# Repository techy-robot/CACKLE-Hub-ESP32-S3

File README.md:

---
modified: 2025-11-07T22:07:35-07:00
---

# ESP32-S3 Hub

> [!TIP]
> This board is part of a larger modular control board ecosystem, [CACKLE](https://github.com/techy-robot/CACKLE)

This is a 4-driver hub based on the Espressif ESP32-S3FH4 chip. It has two cores powerful running at 240 mhz, and 4mb of flash memory. Other variants of the ESP32-S3 can be used as long as they have built in flash memory.

The ESP32-S3 chip does not *quite* have enough pins for driving 4 motors and several sensors, so some cuts were made. For example, on all 4 ports for the ADCs, only two out of three pins are actually connected. This will work for brushed and brushless FOC control, but it may not work for other use cases. I also had to use the USB lines for a tri-state shift register, which controls all the SPI chip select lines. I am planning on programming the chip via UART, which means that the RS485 lines must be disconnected.

The SPI bus should be able to operate at 80mhz, though this has not been tested yet. For all practical use-cases I am limiting this to 20mhz.

Partial 3D picture (headers not shown)

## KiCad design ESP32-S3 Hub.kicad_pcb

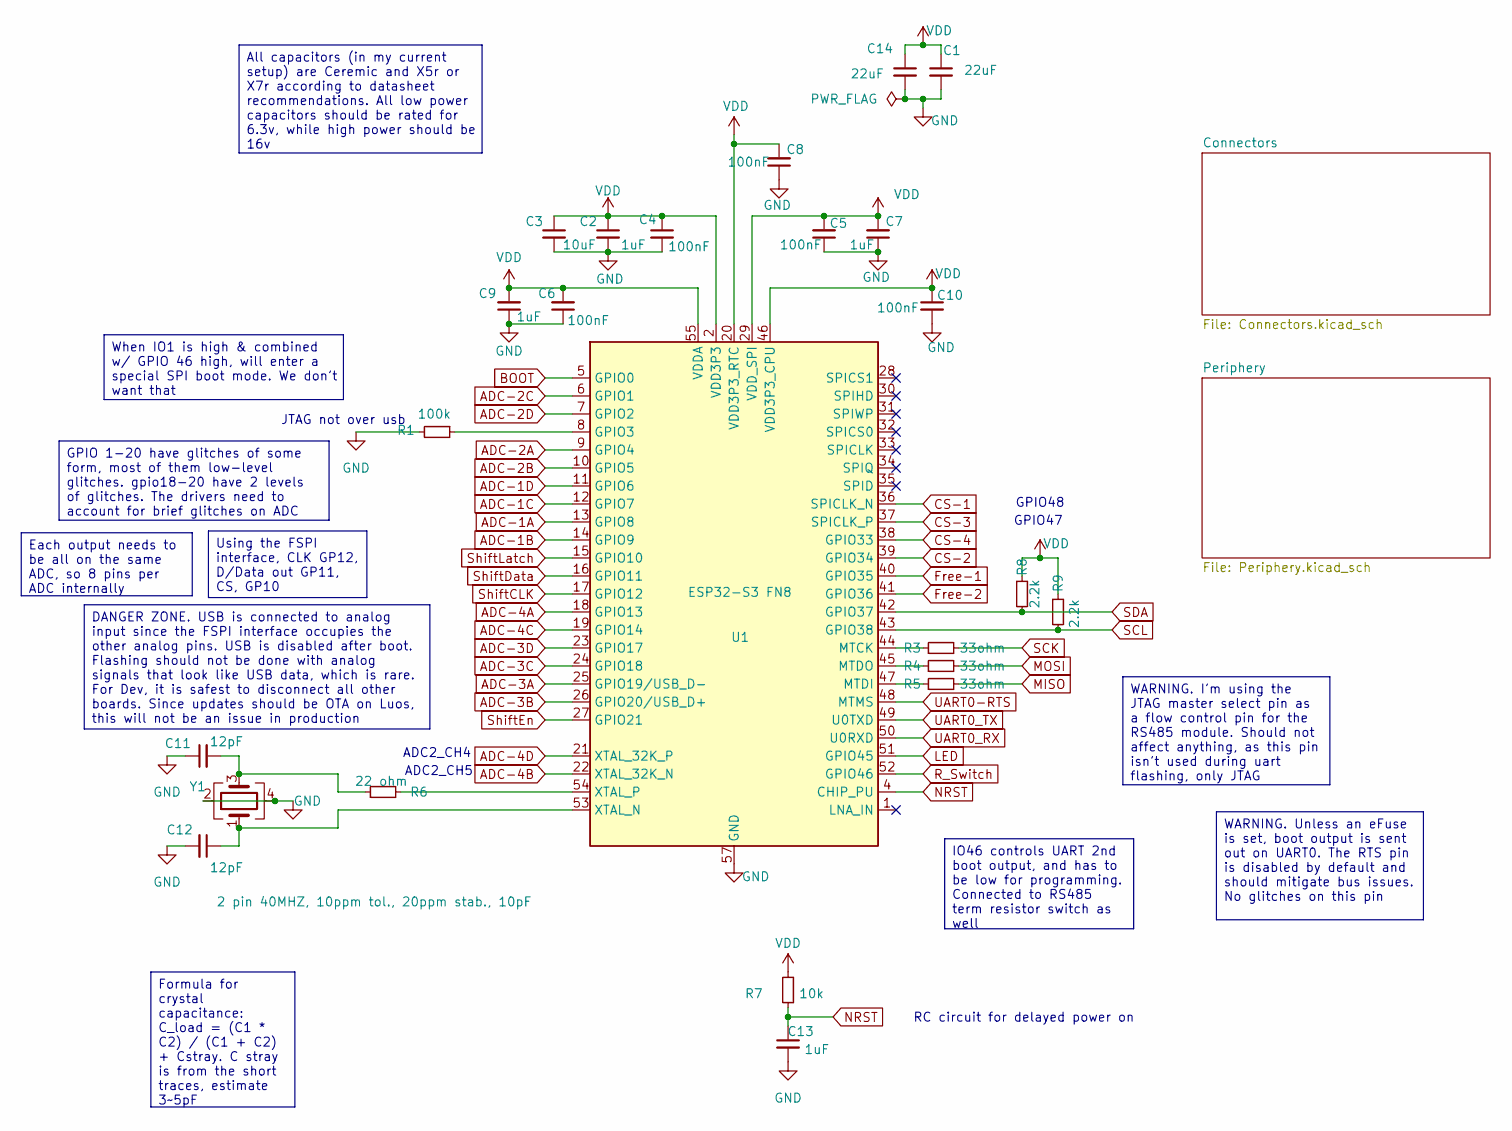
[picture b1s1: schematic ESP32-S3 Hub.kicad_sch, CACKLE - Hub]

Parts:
C1, C14: 22uF; C_0402_1005Metric; LCSC C415703
C2, C7, C9, C13: 1uF; C_0402_1005Metric; LCSC C52923
C3: 10uF; C_0402_1005Metric; LCSC C15525
C4, C5, C6, C8, C10: 100nF; C_0402_1005Metric; LCSC C1525
C11, C12: 12pF; C_0201_0603Metric; LCSC C384960
R1: 100k; R_0402_1005Metric; LCSC C25741
R3, R4, R5: 33ohm; R_0402_1005Metric; LCSC C25105
R6: 22 ohm; R_0201_0603Metric; LCSC C155743
R7: 10k; R_0402_1005Metric; LCSC C25744
R8, R9: 2.2k; R_0402_1005Metric; LCSC C25879
U1: ESP32-S3 FN8; QFN-56-1EP_7x7mm_P0.4mm_EP4x4mm; LCSC C3013940
Y1: 2 pin 40MHZ, 10ppm tol., 20ppm stab., 10pF; Crystal_SMD_1612-4Pin_1.6x1.2mm; LCSC C49158191

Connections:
ADC-1A: U1.13 (GPIO8); also elsewhere on the board
ADC-1B: U1.14 (GPIO9); also elsewhere on the board
ADC-1C: U1.12 (GPIO7); also elsewhere on the board
ADC-1D: U1.11 (GPIO6); also elsewhere on the board
ADC-2A: U1.9 (GPIO4); also elsewhere on the board
ADC-2B: U1.10 (GPIO5); also elsewhere on the board
ADC-2C: U1.6 (GPIO1); also elsewhere on the board
ADC-2D: U1.7 (GPIO2); also elsewhere on the board
ADC-3A: U1.25 (GPIO19/USB_D-); also elsewhere on the board
ADC-3B: U1.26 (GPIO20/USB_D+); also elsewhere on the board
ADC-3C: U1.24 (GPIO18); also elsewhere on the board
ADC-3D: U1.23 (GPIO17); also elsewhere on the board
ADC-4A: U1.18 (GPIO13); also elsewhere on the board
ADC-4B: U1.22 (XTAL_32K_N); also elsewhere on the board
ADC-4C: U1.19 (GPIO14); also elsewhere on the board
ADC-4D: U1.21 (XTAL_32K_P); also elsewhere on the board
BOOT: U1.5 (GPIO0); also elsewhere on the board
CS-1: U1.36 (SPICLK_N); also elsewhere on the board
CS-2: U1.39 (GPIO34); also elsewhere on the board
CS-3: U1.37 (SPICLK_P); also elsewhere on the board
CS-4: U1.38 (GPIO33); also elsewhere on the board
Free-1: U1.40 (GPIO35); also elsewhere on the board
Free-2: U1.41 (GPIO36); also elsewhere on the board
GND: C1.2, C2.2, C3.2, C4.2, C5.1, C6.1, C7.1, C8.1, C9.1, C10.2, C11.1, C12.2, C13.2, C14.2, R1.2, U1.57 (GND), Y1.2, Y1.4; also elsewhere on the board
LED: U1.51 (GPIO45); also elsewhere on the board
MISO: R5.2; also elsewhere on the board
MOSI: R4.2; also elsewhere on the board
NRST: C13.1, R7.1, U1.4 (CHIP_PU); also elsewhere on the board
unnamed: C11.2, R6.1, Y1.3
unnamed: R1.1, U1.8 (GPIO3)
unnamed: R3.1, U1.44 (MTCK)
unnamed: R5.1, U1.47 (MTDI)
unnamed: R4.1, U1.45 (MTDO)
unnamed: C12.1, U1.53 (XTAL_N), Y1.1
unnamed: R6.2, U1.54 (XTAL_P)
R_Switch: U1.52 (GPIO46); also elsewhere on the board
SCK: R3.2; also elsewhere on the board
SCL: R9.2, U1.43 (GPIO38); also elsewhere on the board
SDA: R8.2, U1.42 (GPIO37); also elsewhere on the board
ShiftCLK: U1.17 (GPIO12); also elsewhere on the board
ShiftData: U1.16 (GPIO11); also elsewhere on the board
ShiftEn: U1.27 (GPIO21); also elsewhere on the board
ShiftLatch: U1.15 (GPIO10); also elsewhere on the board
UART0-RTS: U1.48 (MTMS); also elsewhere on the board
UART0_RX: U1.50 (U0RXD); also elsewhere on the board
UART0_TX: U1.49 (U0TXD); also elsewhere on the board
VDD: C1.1, C2.1, C3.1, C4.1, C5.2, C6.2, C7.2, C8.2, C9.2, C10.1, C14.1, R7.2, R8.1, R9.1, U1.2 (VDD3P3), U1.3 (VDD3P3), U1.20 (VDD3P3_RTC), U1.29 (VDD_SPI), U1.46 (VDD3P3_CPU), U1.55 (VDDA), U1.56 (VDDA); also elsewhere on the board

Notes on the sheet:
GPIO48
JTAG not over usb
GPIO47
RC circuit for delayed power on
ADC2_CH4
ADC2_CH5
WARNING. I'm using the JTAG master select pin as a flow control pin for the RS485 module. Should not affect anything, as this pin isn't used during uart flashing, only JTAG
DANGER ZONE. USB is connected to analog input since the FSPI interface occupies the other analog pins. USB is disabled after boot. Flashing should not be done with analog signals that look like USB data, which is rare. For Dev, it is safest to disconnect all other boards. Since updates should be OT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
WARNING. Unless an eFuse is set, boot output is sent out on UART0. The RTS pin is disabled by default and should mitigate bus issues. No glitches on this pin
All capacitors (in my current setup) are Ceremic and X5r or X7r according to datasheet recommendations. All low power capacitors should be rated for 6.3v, while high power should be 16v
IO46 controls UART 2nd boot output, and has to be low for programming. Connected to RS485 term resistor switch as well
Each output needs to be all on the same ADC, so 8 pins per ADC internally
GPIO 1-20 have glitches of some form, most of them low-level glitches. gpio18-20 have 2 levels of glitches. The drivers need to account for brief glitches on ADC
Using the FSPI interface, CLK GP12, D/Data out GP11, CS, GP10
When IO1 is high & combined w/ GPIO 46 high, will enter a special SPI boot mode. We don't want that
Formula for crystal capacitance: C_load = (C1 * C2) / (C1 + C2) + Cstray. C stray is from the short traces, estimate 3~5pF

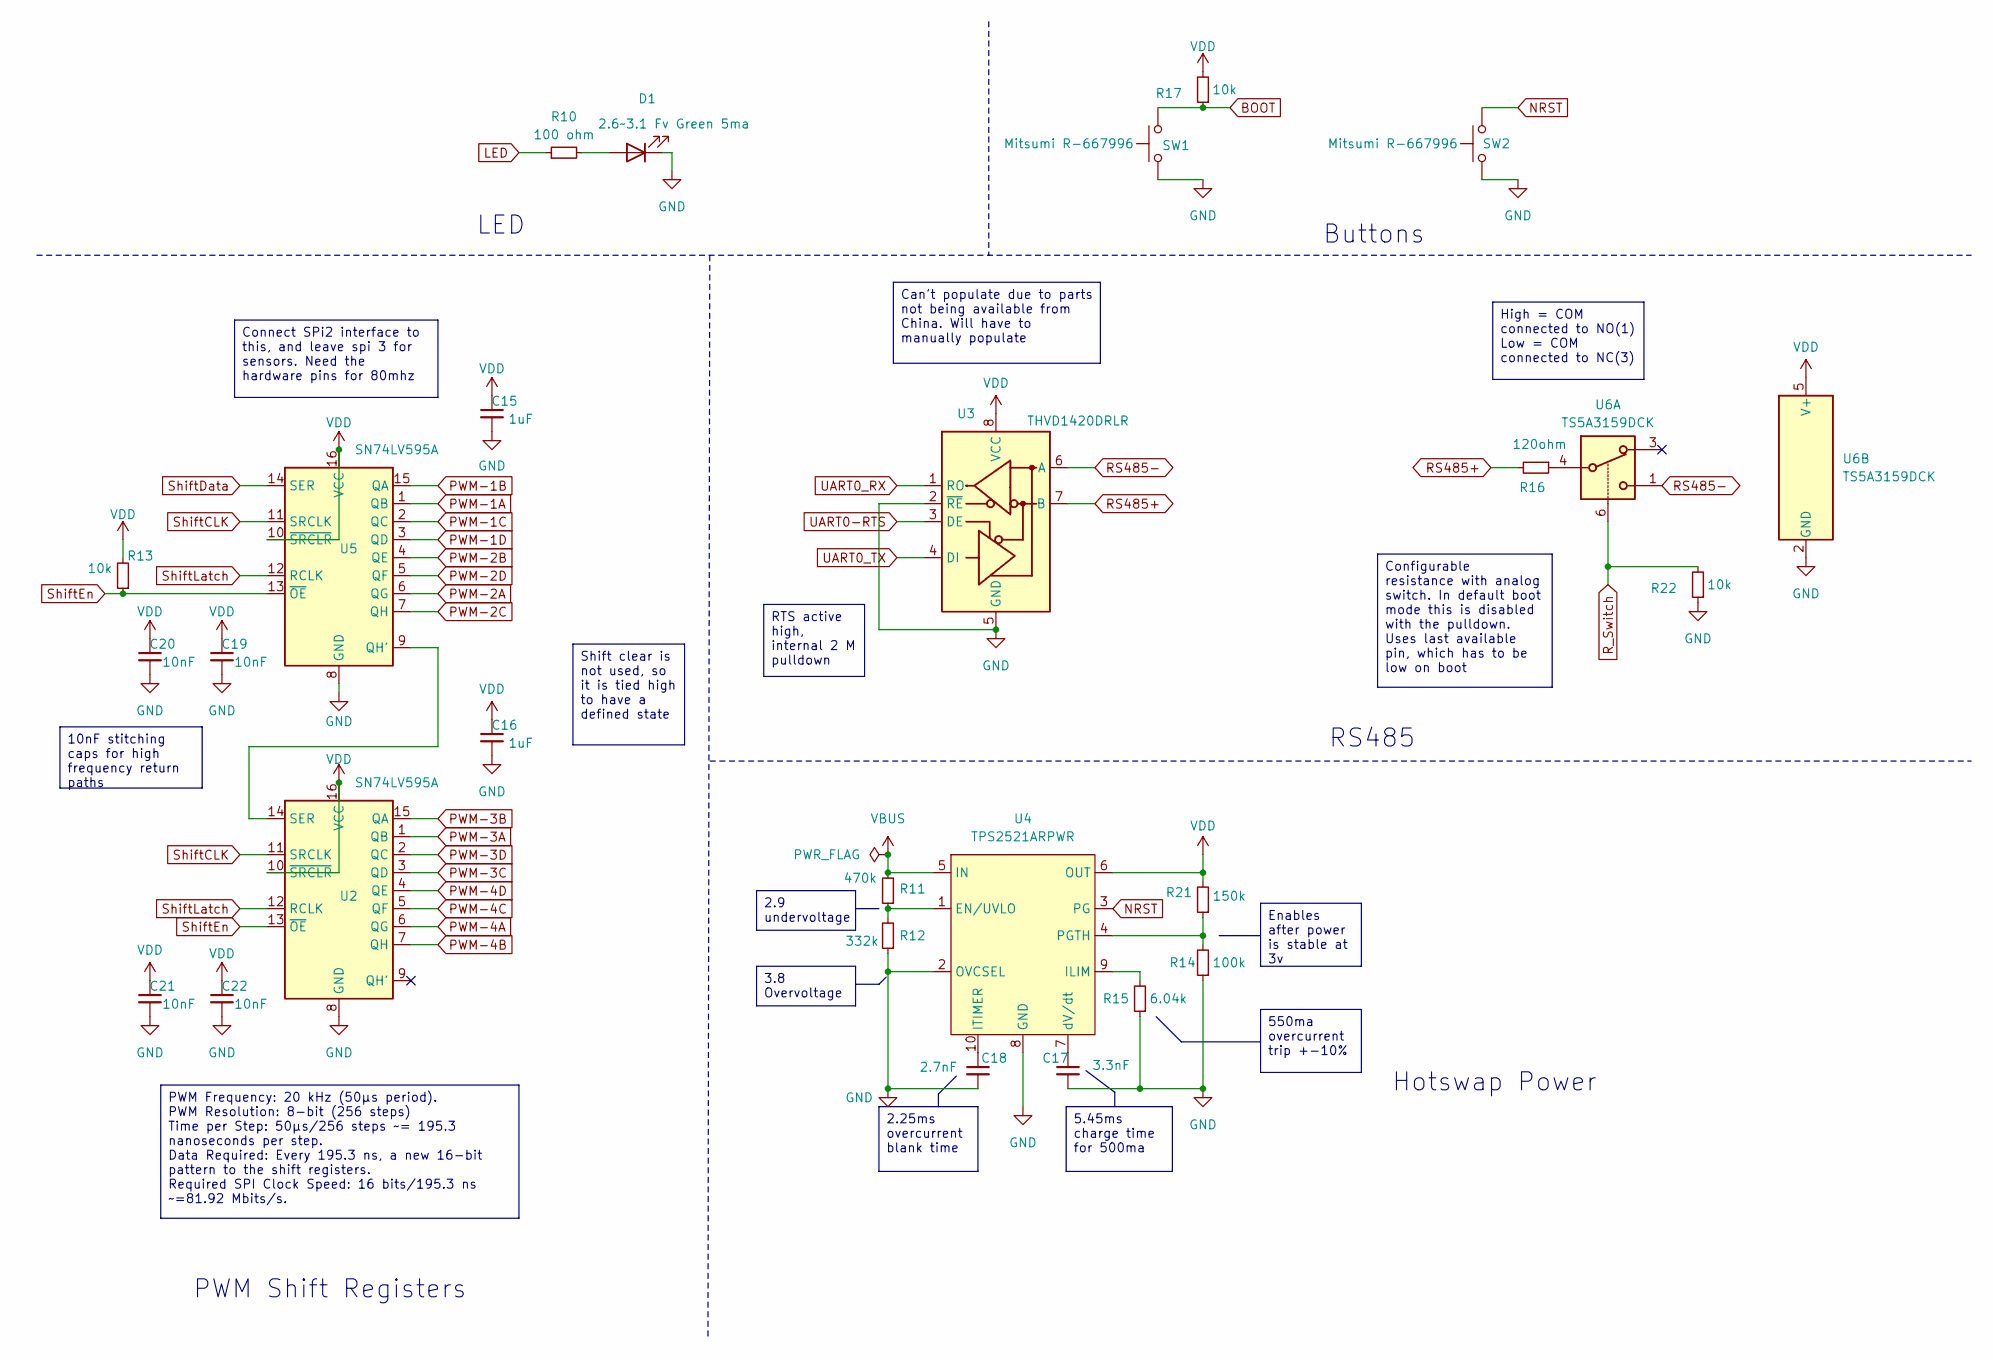
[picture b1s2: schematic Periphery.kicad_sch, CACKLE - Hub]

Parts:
C15, C16: 1uF; C_0402_1005Metric; LCSC C52923
C17: 3.3nF; C_0402_1005Metric; LCSC C272874
C18: 2.7nF; C_0402_1005Metric; LCSC C541392
C19, C20, C21, C22: 10nF; C_0402_1005Metric; LCSC C318576
D1: 2.6~3.1 Fv Green 5ma; LED_0603_1608Metric_Pad1.05x0.95mm_HandSolder; LCSC C3028858
R10: 100 ohm; R_0402_1005Metric; LCSC C185392
R11: 470k; R_0402_1005Metric; LCSC C25790
R12: 332k; R_0402_1005Metric; LCSC C138005
R13, R17, R22: 10k; R_0402_1005Metric; LCSC C25744
R14: 100k; R_0402_1005Metric; LCSC C25741
R15: 6.04k; R_0402_1005Metric; LCSC C321224
R16: 120ohm; R_0402_1005Metric; LCSC C25079
R21: 150k; R_0402_1005Metric; LCSC C25755
SW1, SW2: Mitsumi R-667996; R-667995_MIT; LCSC C4365007
U2, U5: SN74LV595A; DHVQFN-16-1EP_2.5x3.5mm_P0.5mm_EP1x2mm; LCSC C7083313
U3: THVD1420DRLR; SOT-583-8; LCSC C3235555
U4: TPS2521ARPWR; QFN-10_10VQFN_2x2mm_P0.5mm; LCSC C3662707
U6: TS5A3159DCK; SOT-363_SC-70-6; LCSC C46388

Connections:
BOOT: R17.1, SW1.2; also elsewhere on the board
GND: C15.2, C16.2, C17.2, C18.2, C19.2, C20.2, C21.2, C22.2, D1.1 (K), R12.1, R14.1, R15.1, R22.1, SW1.1, SW2.1, U2.8 (GND), U2.17, U3.2 (~RE), U3.5 (GND), U4.2 (OVCSEL), U4.8 (GND), U5.8 (GND), U5.17, U6.2 (GND); also elsewhere on the board
LED: R10.1; also elsewhere on the board
NRST: SW2.2, U4.3 (PG); also elsewhere on the board
unnamed: D1.2 (A), R10.2
unnamed: R16.1, U6.4
unnamed: U2.14 (SER), U5.9 (QH')
unnamed: R11.1, R12.2, U4.1 (EN/UVLO)
unnamed: R15.2, U4.9 (ILIM)
unnamed: C18.1, U4.10 (ITIMER)
unnamed: R14.2, R21.1, U4.4 (PGTH)
unnamed: C17.1, U4.7 (dV/dt)
PWM-1A: U5.1 (QB); also elsewhere on the board
PWM-1B: U5.15 (QA); also elsewhere on the board
PWM-1C: U5.2 (QC); also elsewhere on the board
PWM-1D: U5.3 (QD); also elsewhere on the board
PWM-2A: U5.6 (QG); also elsewhere on the board
PWM-2B: U5.4 (QE); also elsewhere on the board
PWM-2C: U5.7 (QH); also elsewhere on the board
PWM-2D: U5.5 (QF); also elsewhere on the board
PWM-3A: U2.1 (QB); also elsewhere on the board
PWM-3B: U2.15 (QA); also elsewhere on the board
PWM-3C: U2.3 (QD); also elsewhere on the board
PWM-3D: U2.2 (QC); also elsewhere on the board
PWM-4A: U2.6 (QG); also elsewhere on the board
PWM-4B: U2.7 (QH); also elsewhere on the board
PWM-4C: U2.5 (QF); also elsewhere on the board
PWM-4D: U2.4 (QE); also elsewhere on the board
RS485+: R16.2, U3.7 (B); also elsewhere on the board
RS485-: U3.6 (A), U6.1; also elsewhere on the board
R_Switch: R22.2, U6.6; also elsewhere on the board
ShiftCLK: U2.11 (SRCLK), U5.11 (SRCLK); also elsewhere on the board
ShiftData: U5.14 (SER); also elsewhere on the board
ShiftEn: R13.1, U2.13 (~OE), U5.13 (~OE); also elsewhere on the board
ShiftLatch: U2.12 (RCLK), U5.12 (RCLK); also elsewhere on the board
UART0-RTS: U3.3 (DE); also elsewhere on the board
UART0_RX: U3.1 (RO); also elsewhere on the board
UART0_TX: U3.4 (DI); also elsewhere on the board
VBUS: R11.2, U4.5 (IN); also elsewhere on the board
VDD: C15.1, C16.1, C19.1, C20.1, C21.1, C22.1, R13.2, R17.2, R21.2, U2.10 (~SRCLR), U2.16 (VCC), U3.8 (VCC), U4.6 (OUT), U5.10 (~SRCLR), U5.16 (VCC), U6.5 (V+); also elsewhere on the board

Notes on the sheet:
PWM Shift Registers
LED
Buttons
RS485
Hotswap Power
Enables after power is stable at 3v
High = COM connected to NO(1) Low = COM connected to NC(3)
RTS active high, internal 2 M pulldown
Can't populate due to parts not being available from China. Will have to manually populate
Shift clear is not used, so it is tied high to have a defined state
Configurable resistance with analog switch. In default boot mode this is disabled with the pulldown. Uses last available pin, which has to be low on boot
2.25ms overcurrent blank time
10nF stitching caps for high frequency return paths
5.45ms charge time for 500ma
PWM Frequency: 20 kHz (50μs period). PWM Resolution: 8-bit (256 steps) Time per Step: 50μs/256 steps ~= 195.3 nanoseconds per step. Data Required: Every 195.3 ns, a new 16-bit pattern to the shift registers. Required SPI Clock Speed: 16 bits/195.3 ns ~=81.92 Mbits/s.
Connect SPi2 interface to this, and leave spi 3 for sensors. Need the hardware pins for 80mhz
3.8 Overvoltage
550ma overcurrent trip +-10%
2.9 undervoltage

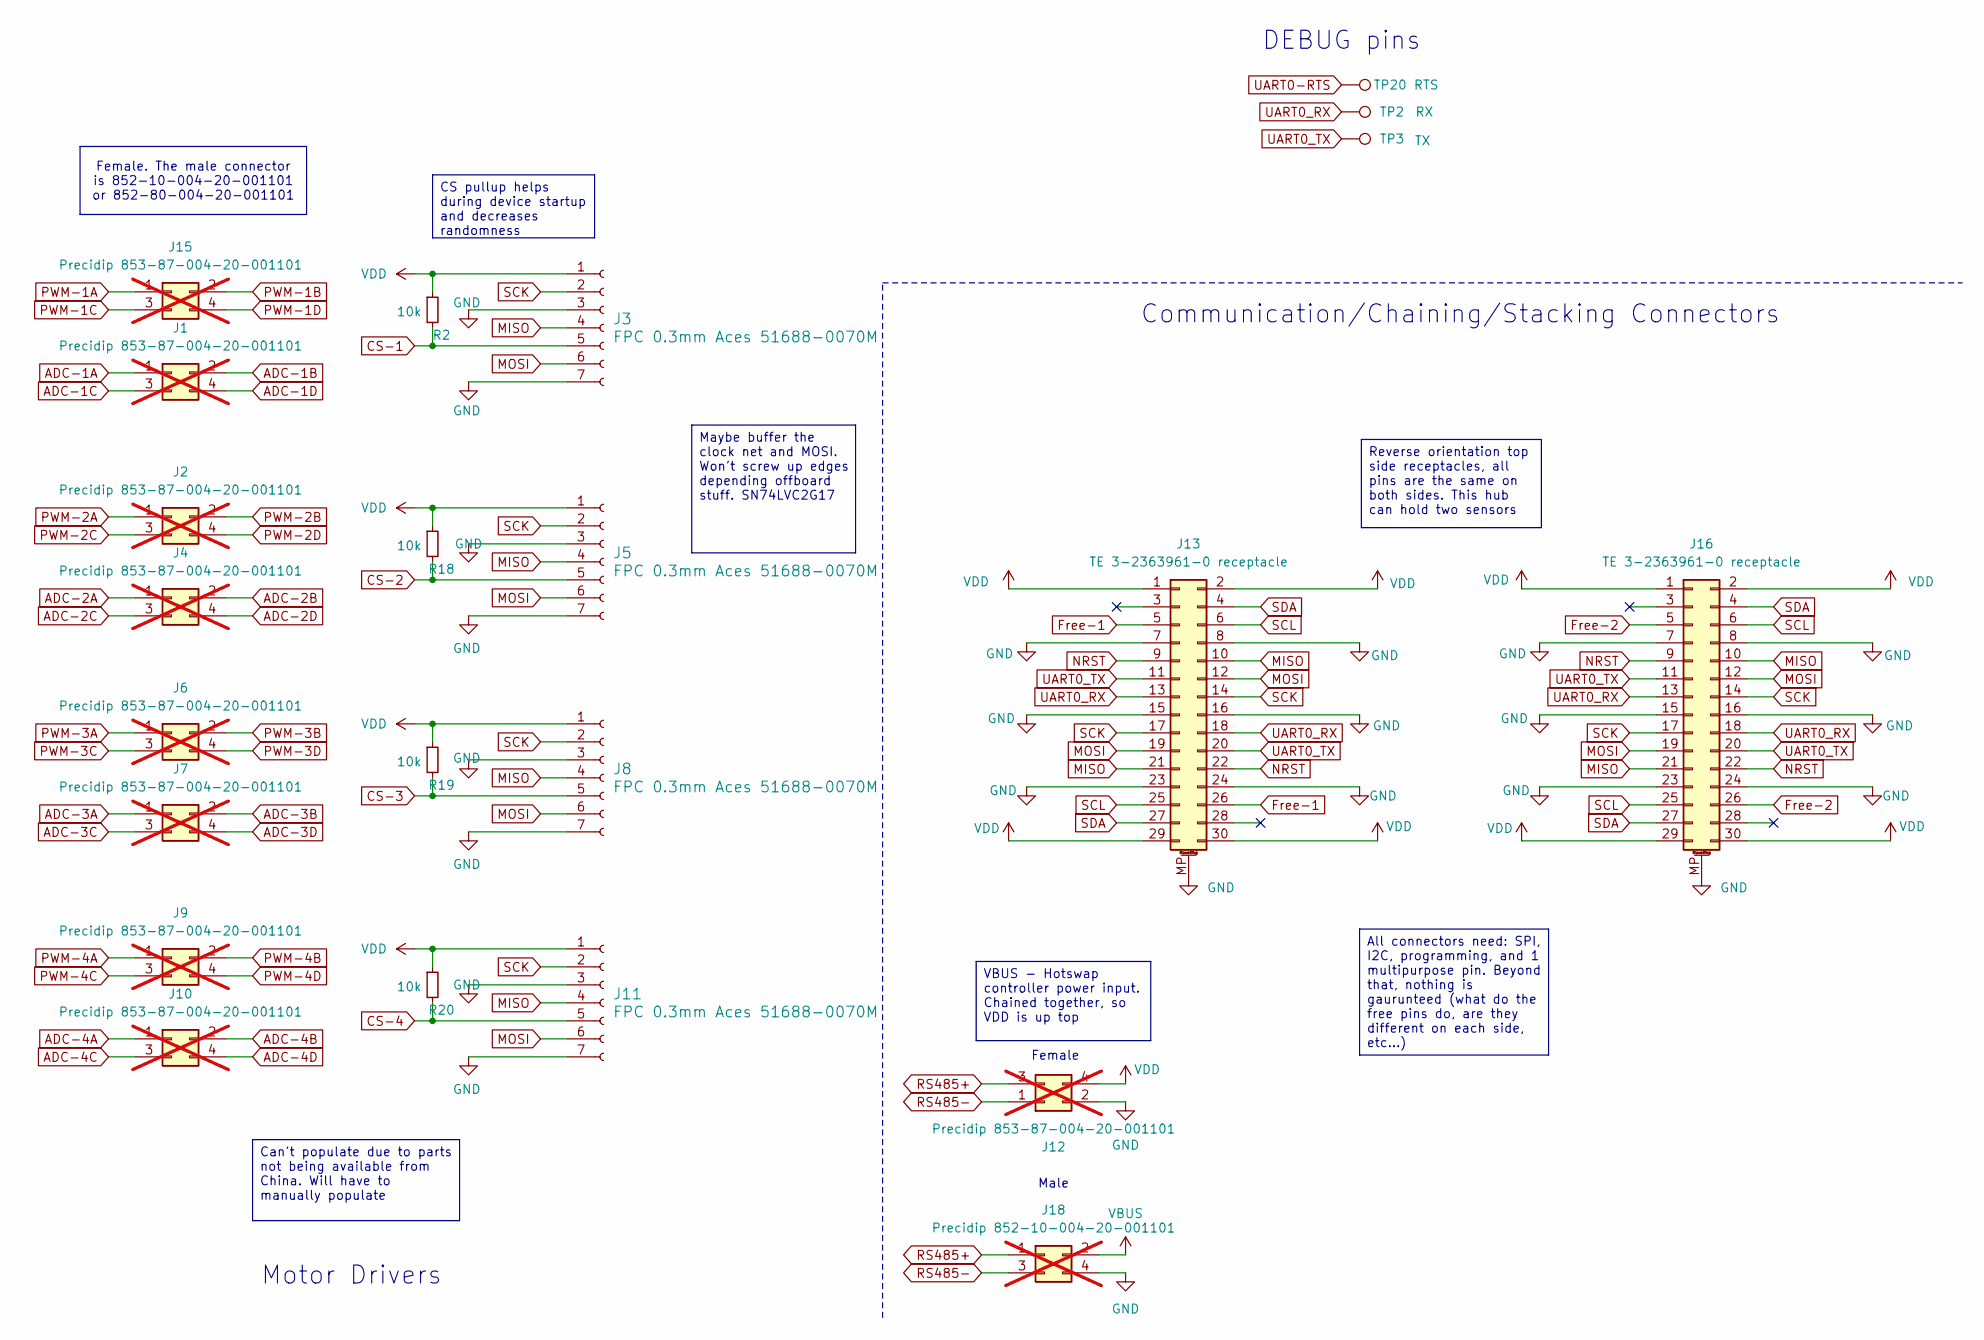
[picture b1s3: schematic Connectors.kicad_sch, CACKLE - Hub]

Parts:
J1, J2, J4, J6, J7, J9, J10, J12, J15: Precidip 853-87-004-20-001101; not fitted
J3, J5, J8, J11: FPC 0.3mm Aces 51688-0070M; fpc_7pin_0.3mm_connector Aces
J13, J16: TE 3-2363961-0 receptacle; TE_mezzanine_rec_3-2363961-0; LCSC C425103
J18: Precidip 852-10-004-20-001101; not fitted
R2, R18, R19, R20: 10k; R_0402_1005Metric; LCSC C25744
TP2: RX; TestPoint_Pad_D1.0mm
TP3: TX; TestPoint_Pad_D1.0mm
TP20: RTS; TestPoint_Pad_D1.0mm

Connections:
ADC-1A: J1.1; also elsewhere on the board
ADC-1B: J1.2; also elsewhere on the board
ADC-1C: J1.3; also elsewhere on the board
ADC-1D: J1.4; also elsewhere on the board
ADC-2A: J4.1; also elsewhere on the board
ADC-2B: J4.2; also elsewhere on the board
ADC-2C: J4.3; also elsewhere on the board
ADC-2D: J4.4; also elsewhere on the board
ADC-3A: J7.1; also elsewhere on the board
ADC-3B: J7.2; also elsewhere on the board
ADC-3C: J7.3; also elsewhere on the board
ADC-3D: J7.4; also elsewhere on the board
ADC-4A: J10.1; also elsewhere on the board
ADC-4B: J10.2; also elsewhere on the board
ADC-4C: J10.3; also elsewhere on the board
ADC-4D: J10.4; also elsewhere on the board
CS-1: J3.5, R2.2; also elsewhere on the board
CS-2: J5.5, R18.2; also elsewhere on the board
CS-3: J8.5, R19.2; also elsewhere on the board
CS-4: J11.5, R20.2; also elsewhere on the board
Free-1: J13.5, J13.26; also elsewhere on the board
Free-2: J16.5, J16.26; also elsewhere on the board
GND: J3.3, J3.7, J5.3, J5.7, J8.3, J8.7, J11.3, J11.7, J12.2, J13.7, J13.8, J13.15, J13.16, J13.23, J13.24, J13.MP (MountPin), J16.7, J16.8, J16.15, J16.16, J16.23, J16.24, J16.MP (MountPin), J18.4; also elsewhere on the board
MISO: J3.4, J5.4, J8.4, J11.4, J13.10, J13.21, J16.10, J16.21; also elsewhere on the board
MOSI: J3.6, J5.6, J8.6, J11.6, J13.12, J13.19, J16.12, J16.19; also elsewhere on the board
NRST: J13.9, J13.22, J16.9, J16.22; also elsewhere on the board
PWM-1A: J15.1; also elsewhere on the board
PWM-1B: J15.2; also elsewhere on the board
PWM-1C: J15.3; also elsewhere on the board
PWM-1D: J15.4; also elsewhere on the board
PWM-2A: J2.1; also elsewhere on the board
PWM-2B: J2.2; also elsewhere on the board
PWM-2C: J2.3; also elsewhere on the board
PWM-2D: J2.4; also elsewhere on the board
PWM-3A: J6.1; also elsewhere on the board
PWM-3B: J6.2; also elsewhere on the board
PWM-3C: J6.3; also elsewhere on the board
PWM-3D: J6.4; also elsewhere on the board
PWM-4A: J9.1; also elsewhere on the board
PWM-4B: J9.2; also elsewhere on the board
PWM-4C: J9.3; also elsewhere on the board
PWM-4D: J9.4; also elsewhere on the board
RS485+: J12.3, J18.1; also elsewhere on the board
RS485-: J12.1, J18.3; also elsewhere on the board
SCK: J3.2, J5.2, J8.2, J11.2, J13.14, J13.17, J16.14, J16.17; also elsewhere on the board
SCL: J13.6, J13.25, J16.6, J16.25; also elsewhere on the board
SDA: J13.4, J13.27, J16.4, J16.27; also elsewhere on the board
UART0-RTS: TP20.1; also elsewhere on the board
UART0_RX: J13.13, J13.18, J16.13, J16.18, TP2.1; also elsewhere on the board
UART0_TX: J13.11, J13.20, J16.11, J16.20, TP3.1; also elsewhere on the board
VBUS: J18.2; also elsewhere on the board
VDD: J3.1, J5.1, J8.1, J11.1, J12.4, J13.1, J13.2, J13.29, J13.30, J16.1, J16.2, J16.29, J16.30, R2.1, R18.1, R19.1, R20.1; also elsewhere on the board

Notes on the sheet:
Male
Communication/Chaining/Stacking Connectors
Motor Drivers
Female
DEBUG pins
Maybe buffer the clock net and MOSI. Won't screw up edges depending offboard stuff. SN74LVC2G17
Reverse orientation top side receptacles, all pins are the same on both sides. This hub can hold two sensors
CS pullup helps during device startup and decreases randomness
Can't populate due to parts not being available from China. Will have to manually populate
All connectors need: SPI, I2C, programming, and 1 multipurpose pin. Beyond that, nothing is gaurunteed (what do the free pins do, are they different on each side, etc...)
VBUS - Hotswap controller power input. Chained together, so VDD is up top
Female. The male connector is 852-10-004-20-001101 or 852-80-004-20-001101

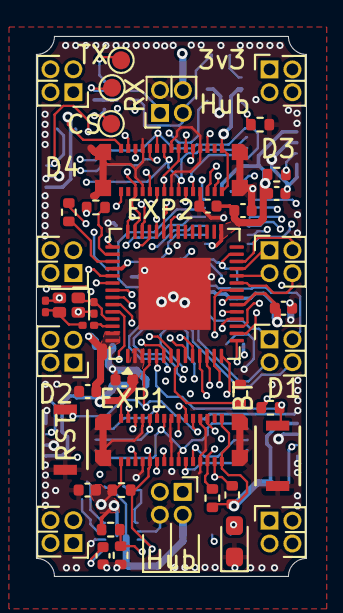
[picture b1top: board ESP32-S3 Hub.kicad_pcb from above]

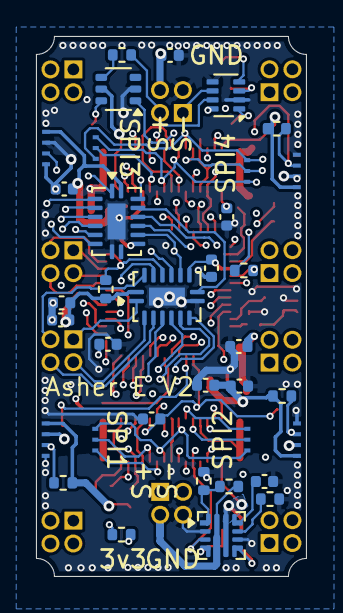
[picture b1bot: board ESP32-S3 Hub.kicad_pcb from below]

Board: 6 copper layers, 15.0 x 30.0 mm, 73 parts (31 on the bottom side), 74 nets.

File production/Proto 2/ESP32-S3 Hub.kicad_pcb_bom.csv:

Designator,Quantity,Value,Footprint,Package,MPN,DNP,Mount_Type,Description,LCSC,Sim.Pins,Rotation Offset
"C1, C14",2,22uF,C_0402_1005Metric,,,,smt,"Unpolarized capacitor, small symbol",C415703,,
"C10, C4, C5, C6, C8",5,100nF,C_0402_1005Metric,,,,smt,"Unpolarized capacitor, small symbol",C1525,,
"C11, C12",2,12pF,C_0402_1005Metric,,,,smt,"Unpolarized capacitor, small symbol",C1547,,
"C13, C15, C16, C2, C7, C9",6,1uF,C_0402_1005Metric,,,,smt,"Unpolarized capacitor, small symbol",C52923,,
C17,1,3.3nF,C_0402_1005Metric,,,,smt,"Unpolarized capacitor, small symbol",C272874,,
C18,1,2.7nF,C_0402_1005Metric,,,,smt,"Unpolarized capacitor, small symbol",C541392,,
"C19, C20, C21, C22",4,10nF,C_0402_1005Metric,,,,smt,"Unpolarized capacitor, small symbol",C318576,,
C3,1,10uF,C_0402_1005Metric,,,,smt,"Unpolarized capacitor, small symbol",C15525,,
D1,1,2.6~3.1 Fv Green 5ma,LED_0603_1608Metric_Pad1.05x0.95mm_HandSolder,,,,smt,Light emitting diode,C3028858,1=K 2=A,
J1,1,Precidip 853-87-004-20-001101,Precidip 853-87-004-20-001101,,,Yes,tht,"Generic connector, double row, 02x02, odd/even pin numbering scheme (row 1 odd numbers, row 2 even numbers), script generated (kicad-library-utils/schlib/autogen/connector/)",,,
J10,1,Precidip 853-87-004-20-001101,Precidip 853-87-004-20-001101,,,Yes,tht,"Generic connector, double row, 02x02, odd/even pin numbering scheme (row 1 odd numbers, row 2 even numbers), script generated (kicad-library-utils/schlib/autogen/connector/)",,,
"J11, J3, J5, J8",4,FPC 0.3mm Aces 51688-0070M,fpc_7pin_0.3mm_connector Aces,,,,smt,"Generic connector, single row, 01x07, script generated",,,
J12,1,Precidip 853-87-004-20-001101,Precidip 853-87-004-20-001101,,,Yes,tht,"Generic connector, double row, 02x02, odd/even pin numbering scheme (row 1 odd numbers, row 2 even numbers), script generated (kicad-library-utils/schlib/autogen/connector/)",,,
"J13, J16",2,TE 3-2363961-0 receptacle,TE_mezzanine_rec_3-2363961-0,,,,smt,"Generic connectable mounting pin connector, double row, 02x15, odd/even pin numbering scheme (row 1 odd numbers, row 2 even numbers), script generated (kicad-library-utils/schlib/autogen/connector/)",C425103,,
J15,1,Precidip 853-87-004-20-001101,Precidip 853-87-004-20-001101,,,Yes,tht,"Generic connector, double row, 02x02, odd/even pin numbering scheme (row 1 odd numbers, row 2 even numbers), script generated (kicad-library-utils/schlib/autogen/connector/)",,,
J18,1,Precidip 852-10-004-20-001101,Precidip 852-10-004-20-001101,,,Yes,tht,"Generic connector, double row, 02x02, odd/even pin numbering scheme (row 1 odd numbers, row 2 even numbers), script generated (kicad-library-utils/schlib/autogen/connector/)",,,
J2,1,Precidip 853-87-004-20-001101,Precidip 853-87-004-20-001101,,,Yes,tht,"Generic connector, double row, 02x02, odd/even pin numbering scheme (row 1 odd numbers, row 2 even numbers), script generated (kicad-library-utils/schlib/autogen/connector/)",,,
J4,1,Precidip 853-87-004-20-001101,Precidip 853-87-004-20-001101,,,Yes,tht,"Generic connector, double row, 02x02, odd/even pin numbering scheme (row 1 odd numbers, row 2 even numbers), script generated (kicad-library-utils/schlib/autogen/connector/)",,,
J6,1,Precidip 853-87-004-20-001101,Precidip 853-87-004-20-001101,,,Yes,tht,"Generic connector, double row, 02x02, odd/even pin numbering scheme (row 1 odd numbers, row 2 even numbers), script generated (kicad-library-utils/schlib/autogen/connector/)",,,
J7,1,Precidip 853-87-004-20-001101,Precidip 853-87-004-20-001101,,,Yes,tht,"Generic connector, double row, 02x02, odd/even pin numbering scheme (row 1 odd numbers, row 2 even numbers), script generated (kicad-library-utils/schlib/autogen/connector/)",,,
J9,1,Precidip 853-87-004-20-001101,Precidip 853-87-004-20-001101,,,Yes,tht,"Generic connector, double row, 02x02, odd/even pin numbering scheme (row 1 odd numbers, row 2 even numbers), script generated (kicad-library-utils/schlib/autogen/connector/)",,,
"R1, R14",2,100k,R_0402_1005Metric,,,,smt,"Resistor, small symbol",C25741,,
R10,1,100 ohm,R_0402_1005Metric,,,,smt,"Resistor, small symbol",C185392,,
R11,1,470k,R_0402_1005Metric,,,,smt,"Resistor, small symbol",C25790,,
R12,1,332k,R_0402_1005Metric,,,,smt,"Resistor, small symbol",C138005,,
"R13, R17, R18, R19, R2, R20, R22, R7, R8, R9",10,10k,R_0402_1005Metric,,,,smt,"Resistor, small symbol",C25744,,
R15,1,6.04k,R_0402_1005Metric,,,,smt,"Resistor, small symbol",C321224,,
R16,1,120ohm,R_0402_1005Metric,,,,smt,"Resistor, small symbol",C25079,,
R21,1,150k,R_0402_1005Metric,,,,smt,"Resistor, small symbol",C25755,,
"R3, R4, R5",3,33ohm,R_0402_1005Metric,,,,smt,"Resistor, small symbol",C25105,,
R6,1,22 ohm,R_0402_1005Metric,,,,smt,"Resistor, small symbol",C25092,,
"SW1, SW2",2,Mitsumi R-667996,R-667995_MIT,,,,smt,"Push button switch, generic, two pins",C4365007,,
U1,1,ESP32-S3 FN8,QFN-56-1EP_7x7mm_P0.4mm_EP4x4mm,,,,smt,"Microcontroller, Wi-Fi 802.11b/g/n, Bluetooth, 32bit",C3013940,,180
"U2, U5",2,SN74LV595A,DHVQFN-16-1EP_2.5x3.5mm_P0.5mm_EP1x2mm,,,,smt,8-bit serial in/out Shift Register 3-State Outputs,C6297201,,
U3,1,THVD1420DRLR,SOT-583-8,,,,smt,"Half duplex RS-485/RS-422, 12 Mbps, 3V - 5.5V supply, ±12kV electro-static discharge (ESD) protection, with receiver/driver enable, 32 receiver drive capacity, SOIC-8",C3235555,,
U4,1,TPS2521ARPWR,QFN-10_10VQFN_2x2mm_P0.5mm,,,,smt,,C3662707,,
U6,1,TS5A3159DCK,SOT-363_SC-70-6,,,,smt,"Single SPDT Analog Switch, 1.65-V to 5.5-V Single-Supply Operation, 1Ohm Ron, SC-70-6",C46388,,
Y1,1,"2 pin 40MHZ, 10ppm tol., 20ppm stab., 10pF",Crystal_SMD_2016-4Pin_2.0x1.6mm,,,,smt,"Four pin crystal, GND on pins 2 and 4",C648973,,

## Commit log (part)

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2024-12-31 Rearranged design files
    Instead of "Kicad" the main design folder is now named "Hardware" since I have gerbers and notes besides the kicad files. I have also put my designs in their proper categories.
2025-01-01 Updated files for JLC DFM checks
2025-01-02 Added schematic PDFs for all boards
2025-01-04 Added gerber zip files
2025-01-13 Added README files for each module
2025-01-13 Changed link names for schematic embeds not displayin
    In Obsidian I can see the pdf embeds perfectly fine, but Github doesn't want to show embedded PDFs. I changed the link alias to "Schematic PDF" so people know what the link is when it doesn't display
2025-02-02 Hardware Revision folder restructuring
2025-03-19 Added pictures to each module
    Next I need to add readmes for each!
2025-10-10 Revert Separation of hardare versions
    This folder versioning will be limited to production files only now
2025-10-10 Started Proto 2 again
2025-10-12 Updated connectors in schem and pcb
2025-10-12 Updated component arrangements and fixed pinout on upstream port
2025-10-17 Removed bottom side connectors due to infeasability for expansion
    Only 4 port mcu hubs could have the double sided expansion unless the MCU was a BGA stuffed away in a corner, so it wouldn't be a common feature. Also it adds a ton of complexity for the RS r485 line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
2025-10-17 Add 5mil traces & 0.4mm vias, started via placement
    I am decreasing the size further to speed up routing and avoid pain. The cost will be higher, but not that much higher from 0.3mm to 0.2mm and 0.6mm to 0.4mm vias. I can route more items.
2025-10-17 Fix some track sizes and clearance issues
2025-10-26 Changed peripheral, tied PWM to shift reg, program pins
2025-10-26 Swapped out footprints on pcb, started routing
2025-10-31 Added future design expansion comments, re arrange components to fit better
2025-10-31 Finish connector schematic
2025-11-01 Swapped around pins and routed main driver outputs
2025-11-01 Finished routing with current components
    I may add some protection and isolation stuff
2025-11-02 Started power protection hotswap circuit
2025-11-03 Replaced LED driver with 2 shift registers
    My initial approach from the first version was better design, I need 80+ mhz to get adequate PWM signals.
2025-11-04 Added configurable termination with analog switch
2025-11-04 Added shift reg footprints
2025-11-04 Got proper values and replacement eFuse
2025-11-05 Reorganized and made schematic clearer
2025-11-05 Corrected footprint, started reconnect nets PCB
2025-11-06 Finished Reroute of ESP32-s3 hub
2025-11-07 Added License
2025-11-08 Moved stencil jig from monorepo to here
2025-11-08 Updated README with link to main repo
2025-11-08 Added software WIP
2025-11-08 Improve schematic consistency
2025-11-08 Removed unnecessary ferrite bead
    There is no radio on this design to worry about power coupling
2025-11-08 Clarified capacitors for main chip
2025-11-08 Fixed ERC power flag issues
2025-11-08 Updated schematic symbols
2025-11-08 Fixed typos with ADC-4 pins, split a few circuits
2025-11-08 Changed LED resistor value to be more standard, reduce brightness
2025-11-10 Added gitignore
2025-11-10 Fixed symbol issue with shift register
2025-11-10 Changed clock schematic layout
2025-11-10 Changed configurable resistor pin in schematic
2025-11-10 Revised routing according to new labels and components
2025-11-10 Added 1 more bulk decop capacitor
2025-11-11 Updated potential spec for buffer
2025-11-11 Decreased number of wires on power plane for more continuous signal
2025-11-11 Exported Schematic pdf
2025-11-11 Added shielding vias all around edge
2025-11-11 Fixed silkscreen and traces according to DRC
2025-11-14 Fixed BOM LCSC part numbers mostly
2025-11-14 Updated 3D models
2025-11-14 Updated Schematic PDF
2025-11-14 Updated Silkscreen, version info
2025-11-14 Aggressive reroute 1 for proper connection
2025-11-14 Added production files and logo to pcb
2025-11-14 Added sponsorship notice
2025-11-15 Updated media
2025-11-21 Fixed clock to be on top only, moved to 0201, separate clock signals
2025-11-21 Removed logo
2025-11-21 Changed i2c resistors to be stronger
    The distance is really short and I was only ever planning on having a few devices per hub, so strength is increased.
2025-11-21 Fixed RS485 skew
2025-11-21 Updated Gerbers
2025-11-21 Added corner 1mm cutouts
    Also excluded some DRC errors and updated 1 footprint
2025-11-21 Found substitute part
2025-11-21 Updated production files
2025-11-21 Fixed missing sub part field in pcb file

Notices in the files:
Connectors.kicad_sch:
Licensed under CERN-OHL-S v2
